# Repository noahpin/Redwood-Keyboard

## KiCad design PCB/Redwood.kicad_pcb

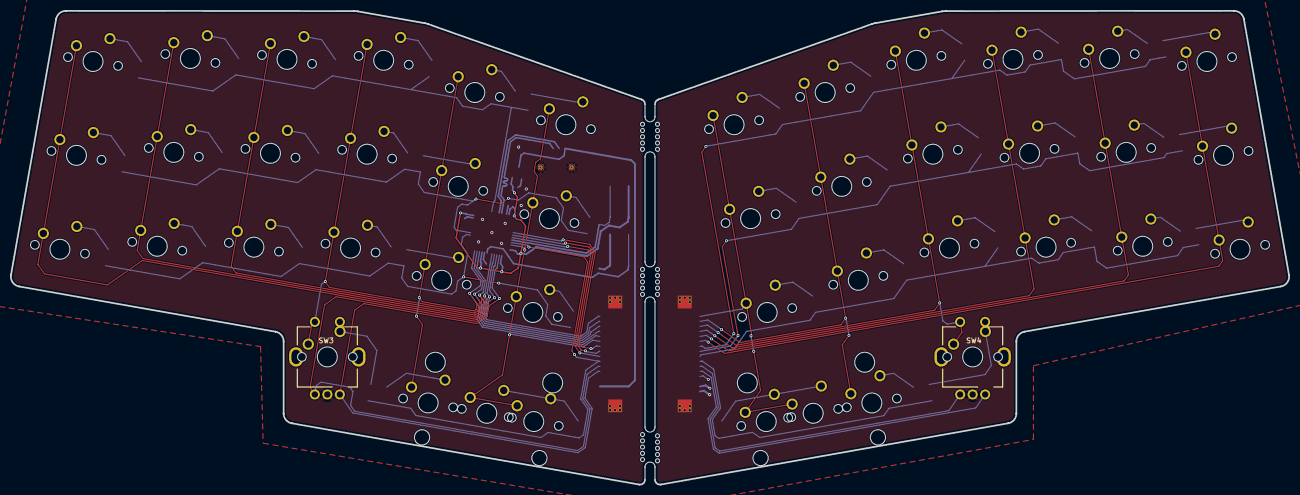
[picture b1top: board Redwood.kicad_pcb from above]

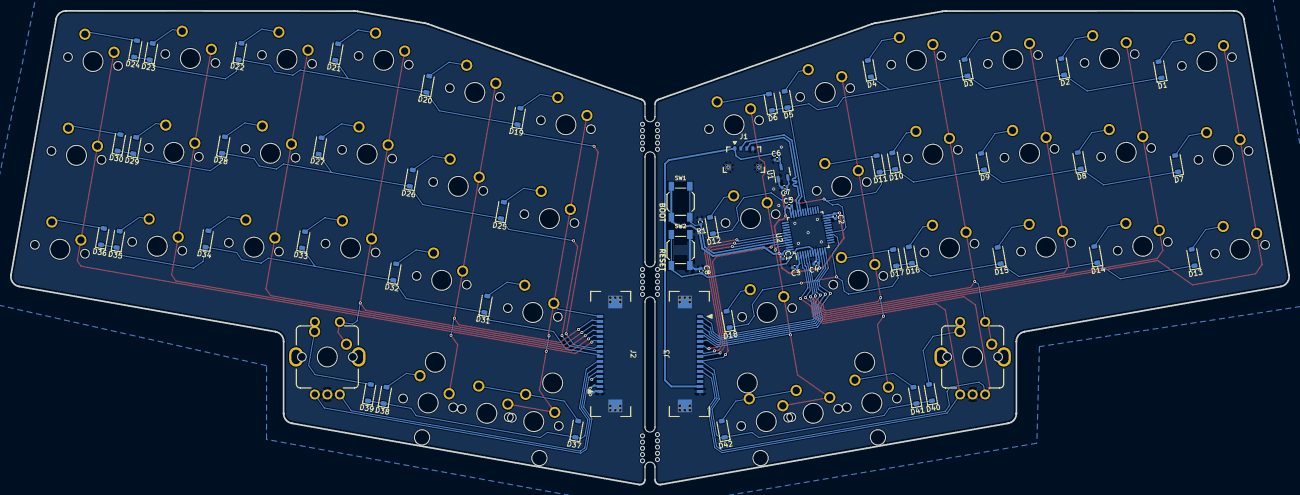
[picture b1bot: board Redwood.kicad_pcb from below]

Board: 2 copper layers, 255.4 x 94.7 mm, 110 parts (58 on the bottom side), 65 nets.

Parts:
C1, C2, C3, C4, C5, C8: 100nF; C_0402_1005Metric
C6, C7: 1uF; C_0402_1005Metric
D1, D2, D3, D4, D5, D6, D7, D8, D9, D10, D11, D12, D13, D14, D15, D16, D17, D18, D19, D20, D21, D22, D23, D24, D25, D26, D28, D29, D30, D31, D32, D33, D34, D35, D36, D37, D38, D39, D40, D41, D42: D_Small; D_SOD-123
D27: 1N4148; D_SOD-123
H1, H2, H3, H4, H5, H6: MountingHole; MouseBite_IPC7351
J1: Conn_01x04_MountingPin; MOLEX_781710004_MountingReliefs
J2, J3: Conn_01x16; XFCN_F1004-H-16-20G-R_P1.0mm_MountingReliefs
R1: 10k; R_0402_1005Metric
SW1: BOOT; SW_SPST_SKQG_WithoutStem
SW2: RESET; SW_SPST_SKQG_WithoutStem
SW3, SW4: EC11Ex; ALPS_EC11E
SW5, SW6, SW7, SW8, SW9, SW10, SW11, SW12, SW13, SW14, SW15, SW16, SW17, SW18, SW19, SW20, SW21, SW22, SW23, SW24, SW25, SW26, SW27, SW28, SW29, SW30, SW31, SW32, SW33, SW34, SW35, SW36, SW37, SW38, SW39, SW40, SW45, SW46, SW47, SW48: SW_Push; MXOnly-1U-NoLED
SW41, SW42: SW_Push; MXOnly-1.25U-NoLED
SW43, SW44: SW_Push; MXOnly-2.25U-ReversedStabilizers-NoLED
U1: XC6206PxxxMR; SOT-23-3
U2: STM32F072C8Tx; LQFP-48_7x7mm_P0.5mm

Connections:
+3.3V: C1.1, C2.1, C3.1, C4.1, C5.1, C7.1, SW1.1, U1.2 (VO), U2.1 (VBAT), U2.9 (VDDA), U2.24 (VDD), U2.36 (VDDIO2), U2.48 (VDD)
+5V: C6.1, J1.1, J2.2, J3.15, U1.3 (VI)
BOOTO: R1.1, SW1.2, U2.44 (BOOT0)
COL0: J2.16, J3.1, SW5.1, SW11.1, SW17.1, SW23.1, SW29.1, SW35.1, SW41.1, SW43.1, U2.4 (PC15)
COL1: J2.15, J3.2, SW6.1, SW12.1, SW18.1, SW24.1, SW30.1, SW36.1, SW45.1, U2.5 (PF0)
COL2: J2.14, J3.3, SW4.S1, SW7.1, SW13.1, SW19.1, SW25.1, SW31.1, SW37.1, SW46.1, U2.10 (PA0)
COL3: J2.13, J3.4, SW3.S1, SW8.1, SW14.1, SW20.1, SW26.1, SW32.1, SW38.1, SW47.1, U2.11 (PA1)
COL4: J2.12, J3.5, SW9.1, SW15.1, SW21.1, SW27.1, SW33.1, SW39.1, SW48.1, U2.12 (PA2)
COL5: J2.11, J3.6, SW10.1, SW16.1, SW22.1, SW28.1, SW34.1, SW40.1, SW42.1, SW44.1, U2.46 (PB9)
DATA_N: J1.2, U2.32 (PA11)
DATA_P: J1.3, U2.33 (PA12)
ENCODER_1S2: D40.2 (A), SW3.S2, SW47.2
ENCODER_2S2: D39.2 (A), SW4.S2, SW46.2
ENCODER_A: J2.6, J3.11, SW3.A, SW4.A, U2.3 (PC14)
ENCODER_B: J2.5, J3.12, SW3.B, SW4.B, U2.2 (PC13)
GND: C1.2, C2.2, C3.2, C4.2, C5.2, C6.2, C7.2, C8.1, J1.4, J1.MP (MountPin), J2.1, J2.MP (MountPin), J3.16, J3.MP (MountPin), R1.2, SW2.1, SW3.C, SW4.C, U1.1 (GND), U2.8 (VSSA), U2.23 (VSS), U2.35 (VSS), U2.47 (VSS)
NRST: C8.2, SW2.2, U2.7 (NRST)
unnamed: D1.2 (A), SW5.2
unnamed: D2.2 (A), SW6.2
unnamed: D3.2 (A), SW7.2
unnamed: D4.2 (A), SW8.2
unnamed: D5.2 (A), SW9.2
unnamed: D6.2 (A), SW10.2
unnamed: D7.2 (A), SW11.2
unnamed: D8.2 (A), SW12.2
unnamed: D9.2 (A), SW13.2
unnamed: D10.2 (A), SW14.2
unnamed: D11.2 (A), SW15.2
unnamed: D12.2 (A), SW16.2
unnamed: D13.2 (A), SW17.2
unnamed: D14.2 (A), SW18.2
unnamed: D15.2 (A), SW19.2
unnamed: D16.2 (A), SW20.2
unnamed: D17.2 (A), SW21.2
unnamed: D18.2 (A), SW22.2
unnamed: D19.2 (A), SW23.2
unnamed: D20.2 (A), SW24.2
unnamed: D21.2 (A), SW25.2
unnamed: D22.2 (A), SW26.2
unnamed: D23.2 (A), SW27.2
unnamed: D24.2 (A), SW28.2
unnamed: D25.2 (A), SW29.2
unnamed: D26.2 (A), SW30.2
unnamed: D27.2 (A), SW31.2
unnamed: D28.2 (A), SW32.2
unnamed: D29.2 (A), SW33.2
unnamed: D30.2 (A), SW34.2
unnamed: D31.2 (A), SW35.2
unnamed: D32.2 (A), SW36.2
unnamed: D33.2 (A), SW37.2
unnamed: D34.2 (A), SW38.2
unnamed: D35.2 (A), SW39.2
unnamed: D36.2 (A), SW40.2
unnamed: D37.2 (A), SW41.2, SW43.2
unnamed: D38.2 (A), SW45.2
unnamed: D41.2 (A), SW48.2
unnamed: D42.2 (A), SW42.2, SW44.2
RGB_LED: J2.4, J3.13
ROW0: D1.1 (K), D2.1 (K), D3.1 (K), D4.1 (K), D5.1 (K), D6.1 (K), U2.29 (PA8)
ROW1: D7.1 (K), D8.1 (K), D9.1 (K), D10.1 (K), D11.1 (K), D12.1 (K), U2.17 (PA7)
ROW2: D13.1 (K), D14.1 (K), D15.1 (K), D16.1 (K), D17.1 (K), D18.1 (K), U2.16 (PA6)
ROW3: D19.1 (K), D20.1 (K), D21.1 (K), D22.1 (K), D23.1 (K), D24.1 (K), J2.10, J3.7, U2.41 (PB5)
ROW4: D25.1 (K), D26.1 (K), D27.1 (K), D28.1 (K), D29.1 (K), D30.1 (K), J2.9, J3.8, U2.42 (PB6)
ROW5: D31.1 (K), D32.1 (K), D33.1 (K), D34.1 (K), D35.1 (K), D36.1 (K), J2.8, J3.9, U2.43 (PB7)
ROW6: D37.1 (K), D38.1 (K), D39.1 (K), D40.1 (K), D41.1 (K), D42.1 (K), J2.7, J3.10, U2.45 (PB8)

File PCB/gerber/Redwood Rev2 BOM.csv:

Designator	Value	Footprint	LCSC Part #
J2 J3	Conn_01x16	XFCN_F1004-H-16-20G-R_P1.0mm_MountingReliefs	C668118
D40 D27 D15 D22 D3 D28 D2 D11 D29 D31 D38 D35 D4 D39 D18 D20 D16 D8 D24 D14 D21 D23 D5 D37 D13 D1 D10 D41 D26 D33 D25 D6 D9 D42 D34 D19 D36 D7 D30 D17 D12 D32	1N4148W	D_SOD-123	C81598
SW1	BOOT	SW_SPST_SKQG_WithoutStem	C116647
SW2	RESET	SW_SPST_SKQG_WithoutStem	C116647
C7 C6	1uF	C_0402_1005Metric	C107372
C2 C5 C3 C8 C1 C4	100nF	C_0402_1005Metric	C60474
J1	Conn_01x04_MountingPin	MOLEX_781710004_MountingReliefs	C528030
R1	10k	R_0402_1005Metric	C25744
U1	XC6206PxxxMR	SOT-23-3	C351446
U2	STM32F072C8Tx	LQFP-48_7x7mm_P0.5mm	C80488

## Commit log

2023-10-14 create project
2023-10-14 add submodules
2023-10-15 schematic work, initial key layout,
2023-10-16 lot of pcb layouts, schematic mostly done
2023-11-02 proto pcb ordered
